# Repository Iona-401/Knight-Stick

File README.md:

# Knight-Stick 🕹️✈️

An open-source, fully 3D-printable flight stick engineered for high-precision simulation, modular assembly, and custom hardware integration.

---

## Overview

Commercial flight simulation gear is often prohibitively expensive or locked into closed ecosystems. **Knight-Stick** bridges that gap by providing a fully customizable, high-performance flight controller that you can manufacture at home using 3D printing and custom electronics.

Designed with a heavy focus on ergonomic feel, mechanical durability, and low-latency input processing, this project brings together mechanical CAD, PCB design, and embedded firmware.

---

## Key Features

* **Ergonomic & Modular CAD:** Designed for additive manufacturing, optimizing print orientation for strength and tactile comfort.
* **Precision Inputs:** Built around low-latency sensor architecture to ensure smooth, dead-zone-free axis tracking and crisp button actuation.
* **Custom Electronics:** Dedicated PCB layout for clean signal routing and reliable peripheral connections.
* **Open Source:** Complete hardware schematics, firmware source code, and STL/CAD files available for modification and community contribution.

---

## Repository Structure

```text
Knight-Stick/
├── cad/          # 3D printable models, mechanical assemblies, and STEP/STL files
├── hardware/     # Schematics, board layouts, and manufacturing files
├── firmware/     # Microcontroller source code and USB HID implementation
└── docs/         # Build guides, wiring diagrams, and assembly instructions

```

---

## Getting Started & Bill of Materials (BOM)

To build your own Knight-Stick, check out the documentation and release files in the respective directories:

1. **Hardware & Electronics:** Review the `hardware/` folder for schematic diagrams and PCB fabrication files.
2. **Mechanical Parts:** Grab the latest printable parts from the `cad/` folder. Ensure you follow recommended print settings for structural rigidity (e.g., adequate infill and wall counts).
3. **Firmware:** Flash the controller using the source code provided in the `firmware/` directory.

---

## Contributing

Contributions, feedback, and forks are always welcome! If you have ideas for improved gimbal geometry, alternative sensor integrations, or firmware enhancements, feel free to open an issue or submit a pull request.

---

## License

This project is open-source. See the repository for license details.

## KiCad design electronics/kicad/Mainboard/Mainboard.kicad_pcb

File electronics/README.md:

# Electronics

This directory contains the complete electronics design for the **Knight Stick**
flight stick, including the schematic, PCB layout, and manufacturing outputs.

The electronics are built around an **ESP32**, providing USB and/or wireless
capabilities suitable for use as a flight simulation controller or general
HID device.

## Contents

- `kicad/`  
  Source design files created with **KiCad**, including:
  - Schematics
  - PCB layout
  - Project configuration files  
  These files represent the authoritative source for the electronics design.

- `gerbers/`  
  Fabrication-ready Gerber and drill files, organized by hardware revision.
  These files can be used directly with PCB manufacturers.

- `bom/`  
  Bill of Materials (BOM) files listing all electronic components required to
  assemble the PCB.

## Manufacturing Notes

- Gerber files are provided for convenience; always refer to the KiCad source
  files if modifications are required.
- Check the BOM and schematic carefully before ordering or assembling boards.

## License

All electronics design files in this directory are licensed under the  
**CERN Open Hardware License v2 – Strongly Reciprocal (CERN-OHL-S)**.

See the root `LICENSE-hardware.txt` file for full license terms.

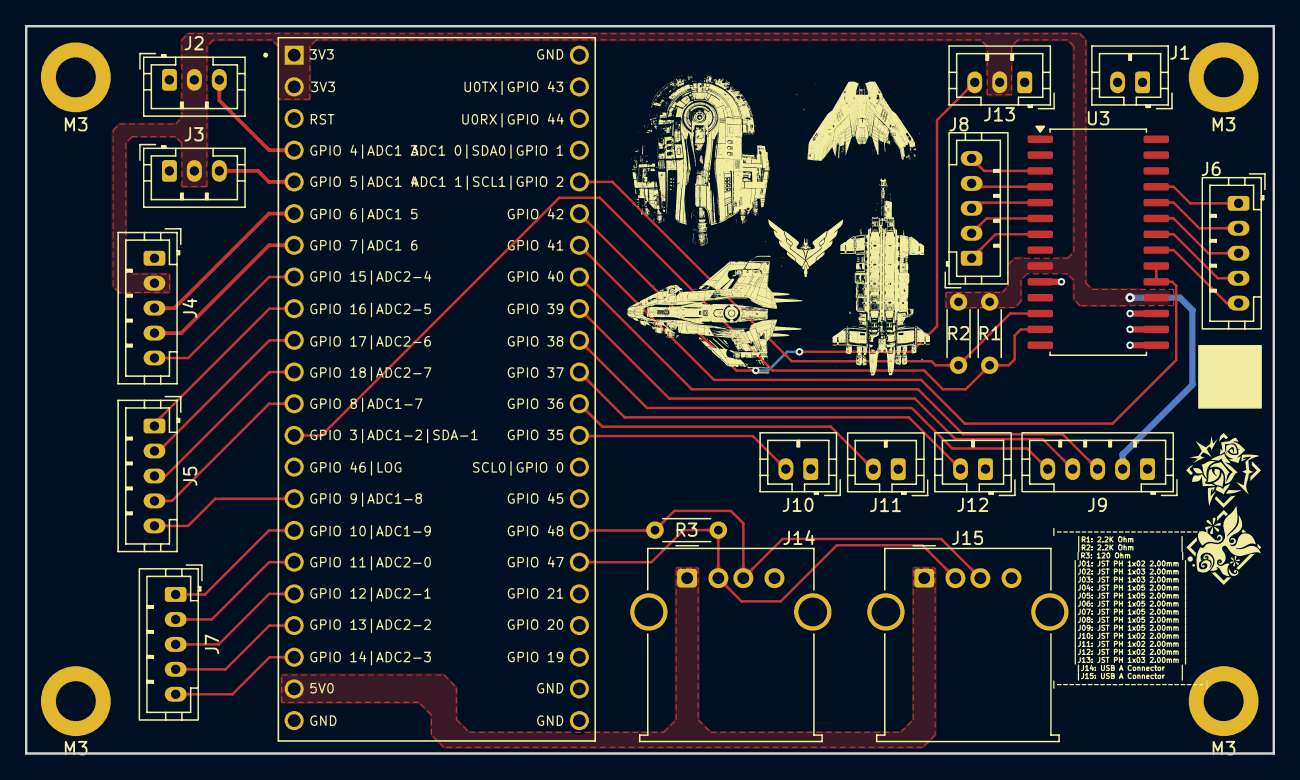
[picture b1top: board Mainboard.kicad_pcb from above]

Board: 2 copper layers, 100.0 x 58.3 mm, 24 parts (0 on the bottom side), 40 nets.

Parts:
J1: GND Pair; JST_PH_B2B-PH-K_1x02_P2.00mm_Vertical
J2: X-Axis Hall; JST_PH_B3B-PH-K_1x03_P2.00mm_Vertical
J3: Y-Axis Hall; JST_PH_B3B-PH-K_1x03_P2.00mm_Vertical
J4, J5, J6, J7, J8, J9: Conn_01x05; JST_PH_B5B-PH-K_1x05_P2.00mm_Vertical
J10: Box Switch 1; JST_PH_B2B-PH-K_1x02_P2.00mm_Vertical
J11: Box Switch 2; JST_PH_B2B-PH-K_1x02_P2.00mm_Vertical
J12: Bos Switch 3; JST_PH_B2B-PH-K_1x02_P2.00mm_Vertical
J13: LED Strip; JST_PH_B3B-PH-K_1x03_P2.00mm_Vertical
J14, J15: USB_A; USB_A_Molex_67643_Horizontal
M3, M3#2, M3#3, M3#4: MountingHole_3.2mm_M3_DIN965_Pad
R1, R2: 2K2; R_Axial_DIN0204_L3.6mm_D1.6mm_P5.08mm_Horizontal
R3: 120; R_Axial_DIN0204_L3.6mm_D1.6mm_P5.08mm_Horizontal
U1: ESP32-S3-DEVKITC-1-N8R2; XCVR_ESP32-S3-DEVKITC-1-N8R2
U3: MCP23017x-x-SO; SOIC-28W_7.5x17.9mm_P1.27mm

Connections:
3V3: J2.2, J3.2, J4.2, J9.2, J13.2, R1.1, R2.1, U1.J1_1 (3V3), U1.J1_2 (3V3), U3.9 (V_{DD}), U3.18 (~RESET)
5V: J14.1 (VBUS), J15.1 (VBUS), U1.J1_21 (5V0)
Base Button: J5.1, U1.J1_9 (GPIO16)
Box Switch 1: J10.2, U1.J3_13 (GPIO35)
Box Switch 2: J11.2, U1.J3_12 (GPIO36)
Box Switch 3: J12.2, U1.J3_11 (GPIO37)
CAN-HI: J14.2 (D-), J15.2 (D-), R3.2, U1.J3_17 (GPIO47)
CAN-LOW: J14.3 (D+), J15.3 (D+), R3.1, U1.J3_16 (GPIO48)
Extra: J13.3, U1.J3_6 (MTMS/GPIO42)
Face Button: J5.3, U1.J1_11 (GPIO18)
Face Hat Left - Center: J6.5, U3.21 (GPA0)
Face Hat Left - Down: J6.3, U3.23 (GPA2)
Face Hat Left - Left: J6.4, U3.22 (GPA1)
Face Hat Left - Right: J6.2, U3.24 (GPA3)
Face Hat Left - Up: J6.1, U3.25 (GPA4)
Face Hat Right - Center: J7.3, U1.J1_18 (GPIO12)
Face Hat Right - Down: J7.1, U1.J1_16 (GPIO10)
Face Hat Right - Left: J7.2, U1.J1_17 (GPIO11)
Face Hat Right - Right: J7.4, U1.J1_19 (GPIO13)
Face Hat Right - Up: J7.5, U1.J1_20 (GPIO14)
GND: J1.1, J1.2, J2.1, J3.1, J4.1, J9.1, J10.1, J11.1, J12.1, J13.1, J14.4 (GND), J14.SH (Shield), J15.4 (GND), J15.SH (Shield), M3.1, M3#2.1, M3#3.1, M3#4.1, U1.J1_22 (GND), U1.J3_1 (GND), U1.J3_21 (GND), U1.J3_22 (GND), U3.10 (V_{SS}), U3.15 (A0), U3.16 (A1), U3.17 (A2)
Head Button: J5.2, U1.J1_10 (GPIO17)
INT: U1.J3_7 (MTDI/GPIO41), U3.19 (INTB), U3.20 (INTA)
Joystick Button: J4.5, U1.J1_8 (GPIO15)
Joystick X: J4.3, U1.J1_6 (GPIO6)
Joystick Y: J4.4, U1.J1_7 (GPIO7)
Primary Trigger: J5.5, U1.J1_15 (GPIO9)
RE A: J9.4, U1.J3_9 (MTCK/GPIO39)
RE B: J9.5, U1.J3_10 (GPIO38)
RE Switch: J9.3, U1.J3_8 (MTDO/GPIO40)
SCK: R2.2, U1.J3_5 (GPIO2), U3.12 (SCK)
SDA: R1.2, U1.J1_13 (GPIO3), U3.13 (SDA)
Secondary Trigger: J5.4, U1.J1_12 (GPIO8)
Thumb Hat - Center: J8.2, U3.6 (GPB5)
Thumb Hat - Down: J8.5, U3.3 (GPB2)
Thumb Hat - Left: J8.1, U3.7 (GPB6)
Thumb Hat - Right: J8.4, U3.4 (GPB3)
Thumb Hat - Up: J8.3, U3.5 (GPB4)
X-Axis: J2.3, U1.J1_4 (GPIO4)
Y-Axis: J3.3, U1.J1_5 (GPIO5)

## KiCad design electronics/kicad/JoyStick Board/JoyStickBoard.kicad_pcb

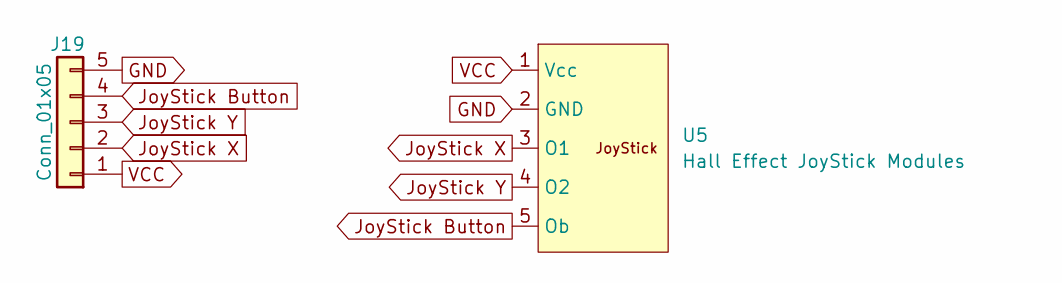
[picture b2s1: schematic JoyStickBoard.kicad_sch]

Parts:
J19: Conn_01x05; JST_PH_B5B-PH-K_1x05_P2.00mm_Vertical
U5: Hall Effect JoyStick Modules; Generic 2 axis Joystick with button

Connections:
GND: J19.5, U5.2 (GND)
JoyStick Button: J19.4, U5.5 (Ob)
JoyStick X: J19.2, U5.3 (O1)
JoyStick Y: J19.3, U5.4 (O2)
VCC: J19.1, U5.1 (Vcc)

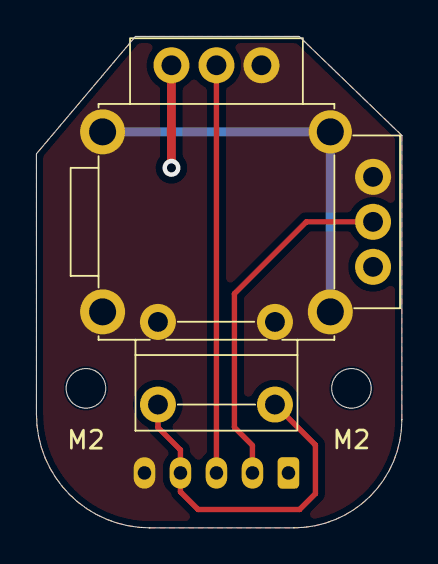
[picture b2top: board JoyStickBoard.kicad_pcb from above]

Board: 2 copper layers, 20.3 x 27.3 mm, 4 parts (1 on the bottom side), 5 nets.

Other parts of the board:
M2, M2#2: MountingHole_2.2mm_M2_DIN965_Pad

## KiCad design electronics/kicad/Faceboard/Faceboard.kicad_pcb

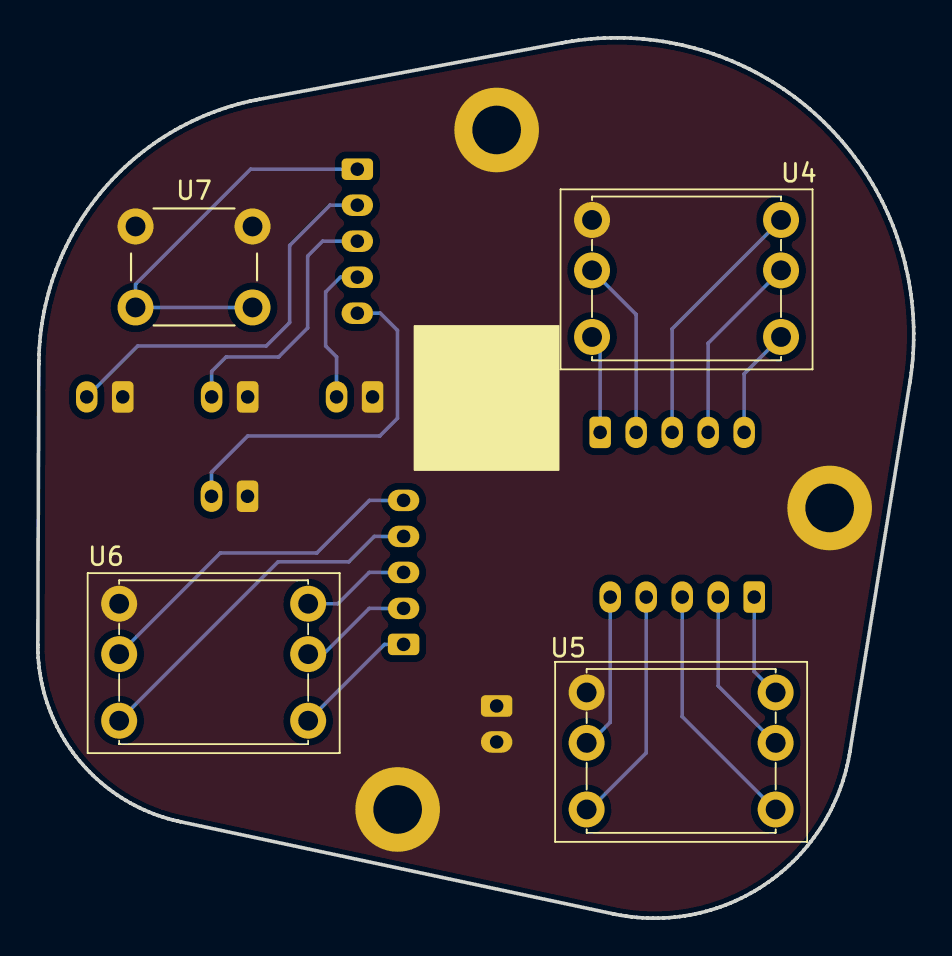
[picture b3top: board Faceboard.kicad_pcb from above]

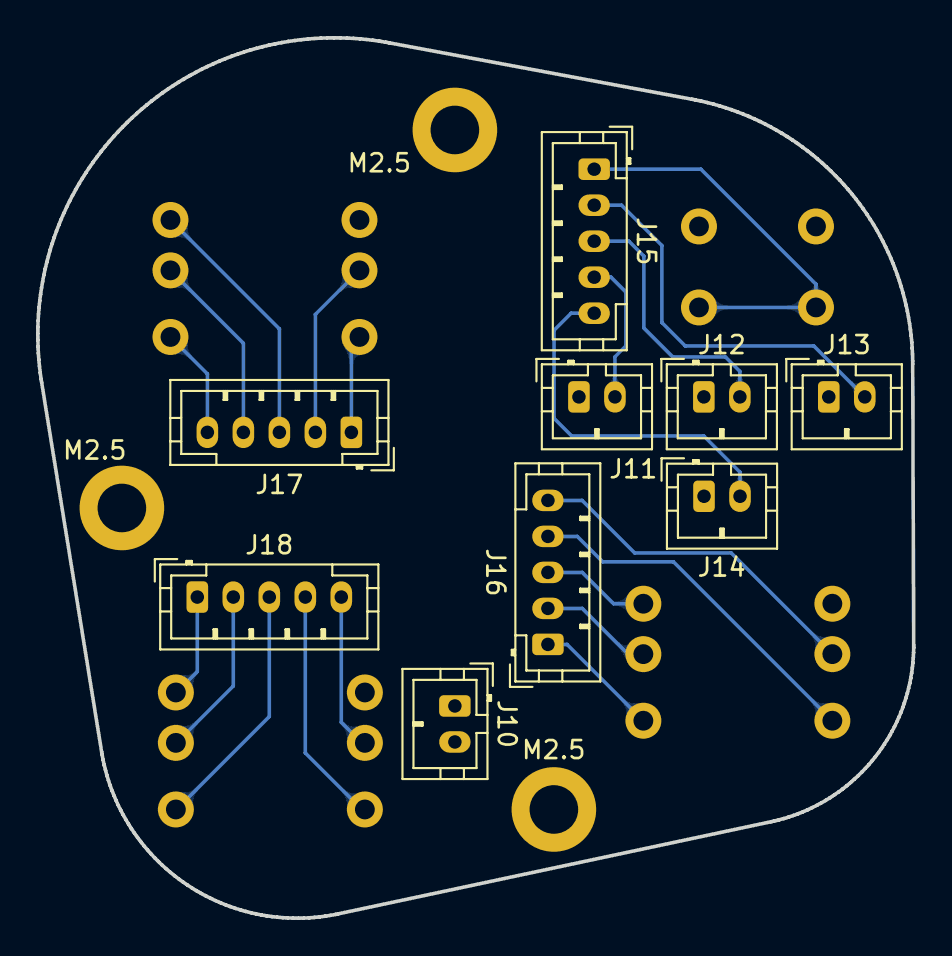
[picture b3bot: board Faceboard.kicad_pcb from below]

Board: 2 copper layers, 48.7 x 48.9 mm, 16 parts (12 on the bottom side), 21 nets.

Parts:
J10: Gnd; JST_PH_B2B-PH-K_1x02_P2.00mm_Vertical
J11: Primary Trigger 1; JST_PH_B2B-PH-K_1x02_P2.00mm_Vertical
J12: Secondary Trigger; JST_PH_B2B-PH-K_1x02_P2.00mm_Vertical
J13: Head Button; JST_PH_B2B-PH-K_1x02_P2.00mm_Vertical
J14: Base Button; JST_PH_B2B-PH-K_1x02_P2.00mm_Vertical
J15, J16, J17, J18: Conn_01x05; JST_PH_B5B-PH-K_1x05_P2.00mm_Vertical
M2.5, M2.5#2, M2.5#3: MountingHole_2.7mm_M2.5_DIN965_Pad
U4: Face Hat Top; 5-Way_Tact_Swt_6-pin
U5: Face Hat Right; 5-Way_Tactile_Swt_6-pin
U6: Face Hat Left; 5-Way_Tactile_Swt_6-pin
U7: Face Button; SW_PUSH_6mm_H5mm

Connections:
Base Button: J14.2, J15.5
Face Button: J15.1, U7.2
Face Hat Left - Center: J18.4, U6.3 (Center)
Face Hat Left - Down: J18.3, U6.6 (Down)
Face Hat Left - Left: J18.5, U6.2 (Left)
Face Hat Left - Right: J18.2, U6.5 (Right)
Face Hat Left - Up: J18.1, U6.4 (Up)
Face Hat Right - Center: J16.4, U5.3 (Center)
Face Hat Right - Down: J16.1, U5.6 (Down)
Face Hat Right - Left: J16.5, U5.2 (Left)
Face Hat Right - Right: J16.2, U5.5 (Right)
Face Hat Right - Up: J16.3, U5.4 (Up)
GND: J10.1, J10.2, J11.1, J12.1, J13.1, J14.1, M2.5.1, M2.5#2.1, M2.5#3.1, U4.1 (GND), U5.1 (GND), U6.1 (GND), U7.1
Head Button: J13.2, J15.2
Primary Trigger 1: J11.2, J15.4
Secondary Trigger: J12.2, J15.3
Thumb Hat - Center: J17.1, U4.3 (Center)
Thumb Hat - Down: J17.5, U4.6 (Down)
Thumb Hat - Left: J17.2, U4.2 (Left)
Thumb Hat - Right: J17.4, U4.5 (Right)
Thumb Hat - Up: J17.3, U4.4 (Up)

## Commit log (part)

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2026-03-21 Add CERN Open Hardware Licence Version 2 document
2026-03-21 Add MIT License to the project
2026-03-21 changed license to license-software
2026-03-21 Add README files for electronics and firmware directories
2026-03-21 Added 3D Print README and STEP Files
    Added all the STEP Files for the Flight stick and modified the readme to reflect the print list.
    Added a base print profile for Orca Slicer.
2026-03-23 Added all KiCad schematics. PCBs, projects files, and all related gerbers
2026-03-23 Updates gerbers to include QR Code patch for JLCPCB
2026-03-23 Enhance README with detailed electronics design info
    Expanded README to include details about the Knight Stick flight stick and its components.
2026-03-23 Revise README for Knight Stick mechanical design
    Updated README to include detailed descriptions of mechanical design files and 3D printing notes.
2026-03-23 Mark firmware as work in progress
    Added a note indicating that the firmware is a work in progress.
2026-03-24 Updated Print Files to current version
2026-04-13 Updated PCB with New Silkscreen
